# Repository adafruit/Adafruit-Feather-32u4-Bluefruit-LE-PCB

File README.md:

## Adafruit Feather 32u4 Bluefruit LE PCB

<a href="http://www.adafruit.com/products/2829"><br/>
Click here to purchase one from the Adafruit shop</a>

PCB files for the Adafruit Feather 32u4 Bluefruit LE. Format is EagleCAD schematic and board layout

For more details, check out the product page at
* https://www.adafruit.com/product/2829

### Description

Feather is the new development board from Adafruit, and like its namesake it is thin, light, and lets you fly! We designed Feather to be a new standard for portable microcontroller cores.

This is the Adafruit Feather 32u4 Bluefruit - our take on an 'all-in-one' Arduino-compatible + Bluetooth Low Energy with built in USB and battery charging. Its an Adafruit Feather 32u4 with a BTLE module, ready to rock! We have other boards in the Feather family, check'em out here.

Bluetooth Low Energy is the hottest new low-power, 2.4GHz spectrum wireless protocol. In particular, its the only wireless protocol that you can use with iOS without needing special certification and it's supported by all modern smart phones. This makes it excellent for use in portable projects that will make use of an iOS or Android phone or tablet. It also is supported in Mac OS X and Windows 8+.

[We have quite a few BTLE-capable Feathers (it's a popular protocol!) so check out our BT Feather guide for some comparison information](https://learn.adafruit.com/adafruit-feather/bluetooth-feathers).

At the Feather 32u4's heart is at ATmega32u4 clocked at 8 MHz and at 3.3V logic, a chip setup we've had tons of experience with as it's the same as the Flora. This chip has 32K of flash and 2K of RAM, with built in USB so not only does it have a USB-to-Serial program & debug capability built in with no need for an FTDI-like chip, it can also act like a mouse, keyboard, USB MIDI device, etc.

To make it easy to use for portable projects, we added a connector for any of our 3.7V Lithium polymer batteries and built in battery charging. You don't need a battery, it will run just fine straight from the micro USB connector. But, if you do have a battery, you can take it on the go, then plug in the USB to recharge. The Feather will automatically switch over to USB power when its available. We also tied the battery thru a divider to an analog pin, so you can measure and monitor the battery voltage to detect when you need a recharge.

### License

Adafruit invests time and resources providing this open source design, please support Adafruit and open-source hardware by purchasing products from [Adafruit](https://www.adafruit.com)!

Designed by Limor Fried/Ladyada for Adafruit Industries.

Creative Commons Attribution/Share-Alike, all text above must be included in any redistribution. See license.txt for additional details.

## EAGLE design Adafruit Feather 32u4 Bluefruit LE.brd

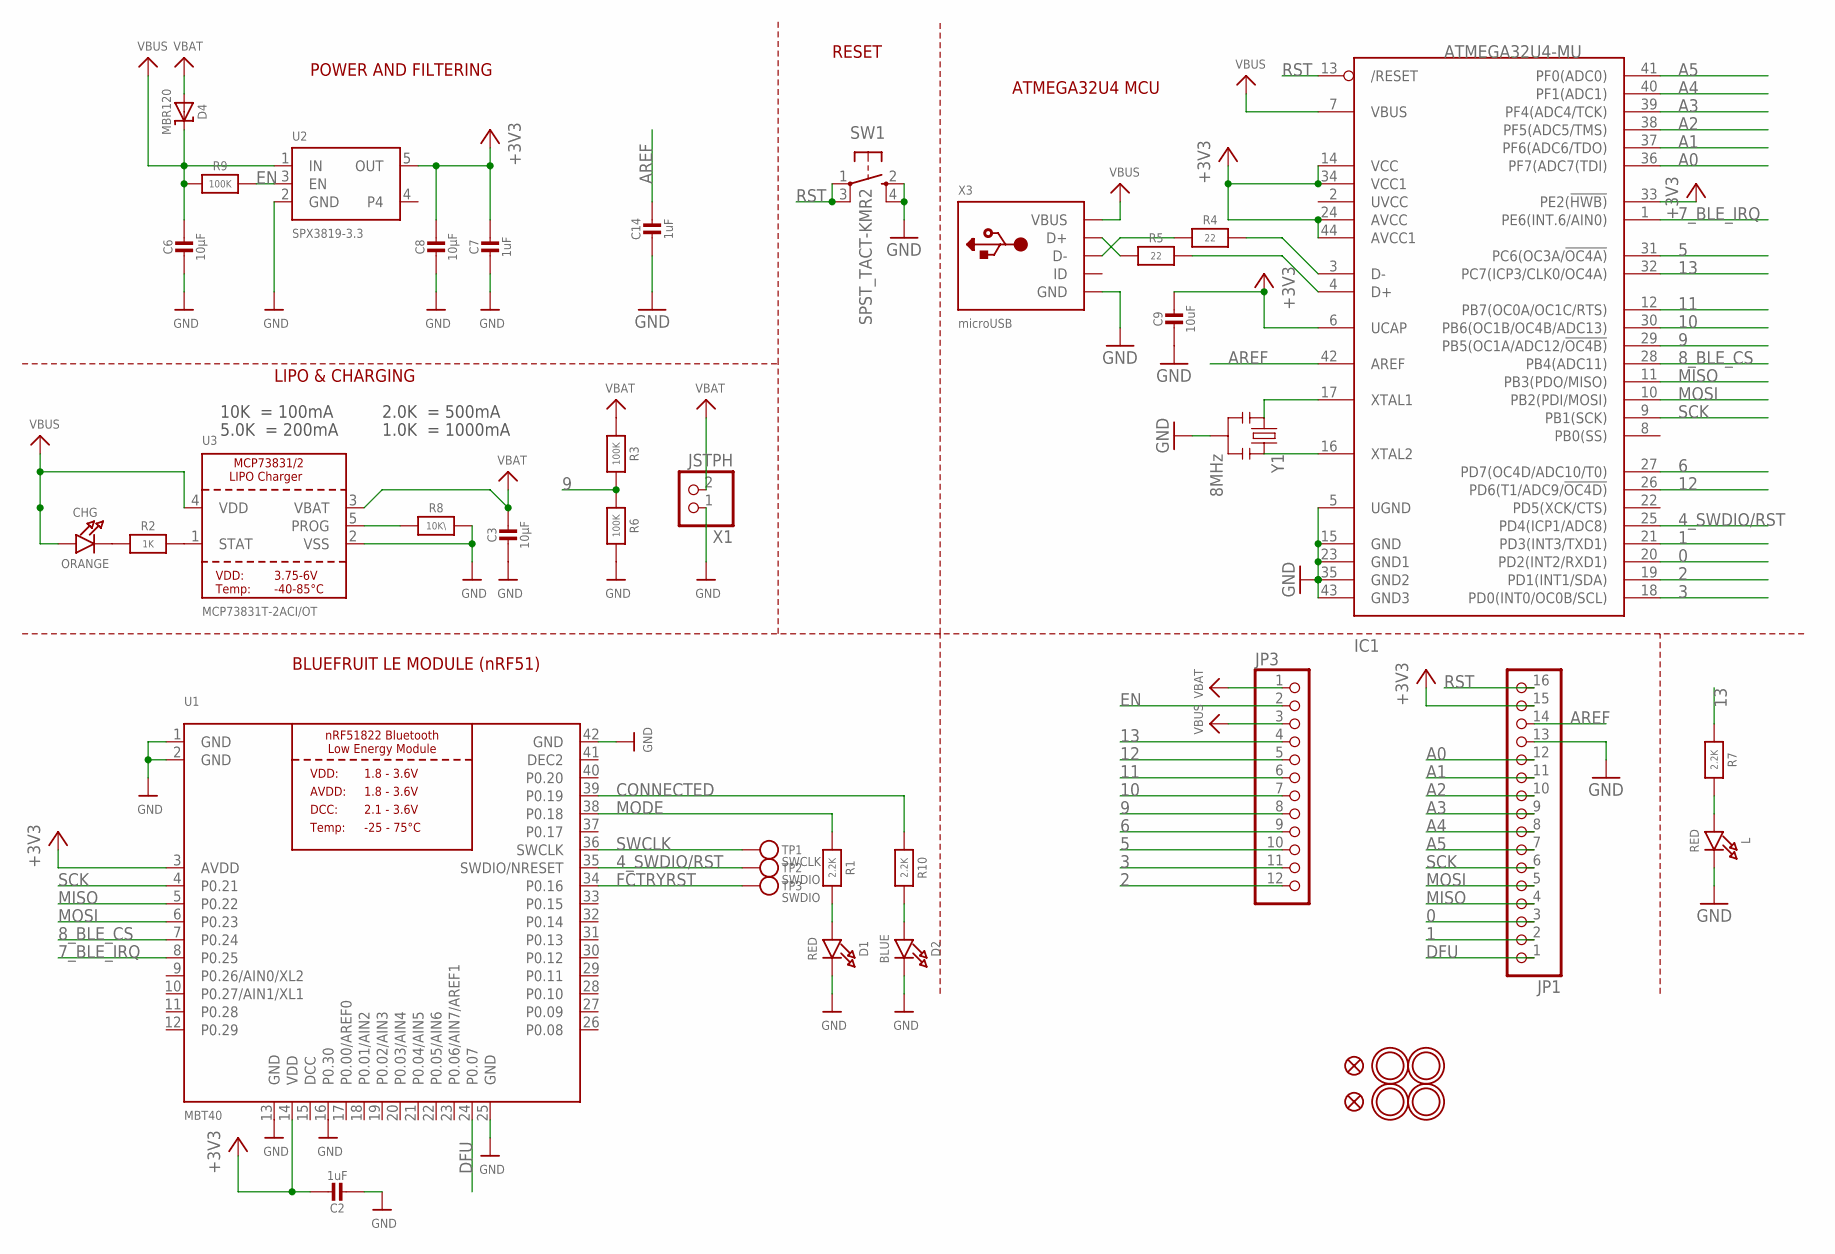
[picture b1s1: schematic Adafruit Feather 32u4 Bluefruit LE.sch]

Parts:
C2, C7, C14: 1uF; 0603-NO
C3, C6, C8: 10µF; 0805-NO
C9: 10uF; _0805MP
CHG: ORANGE; CHIPLED_0805_NOOUTLINE
D1: RED; CHIPLED_0805_NOOUTLINE
D2: BLUE; CHIPLED_0805_NOOUTLINE
D4: MBR120; SOD-123
IC1: ATMEGA32U4-MU; TQFN44_7MM
JP1: HEADER-1X16ROUND; 1X16_ROUND
JP3: HEADER-1X12; 1X12_ROUND
L: RED; CHIPLED_0805_NOOUTLINE
R1, R7, R10: 2.2K; 0603-NO
R2: 1K; 0603-NO
R3, R6, R9: 100K; 0603-NO
R4, R5: 22; 0603-NO
R8: 10K\; 0603-NO
SW1: SPST_TACT-KMR2; KMR2
TP1: SWCLK; PAD-1.5X2.0
TP2, TP3: SWDIO; PAD-1.5X2.0
U1: MBT40; BLE_MODULE_RAYTAC_MDBT40
U2: SPX3819-3.3; SOT23-5
U3: MCP73831T-2ACI/OT; SOT23-5
U$6, U$24, U$31, U$32: MOUNTINGHOLE2.5; MOUNTINGHOLE_2.5_PLATED
U$34, U$35: FIDUCIAL""; FIDUCIAL_1MM
X1: JSTPH; JSTPH2
X3: microUSB; 4UCONN_20329_V2
Y1: 8MHz; RESONATOR-SMD

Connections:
0: IC1.20 (PD2(INT2/RXD1)), JP1.3
1: IC1.21 (PD3(INT3/TXD1)), JP1.2
2: IC1.19 (PD1(INT1/SDA)), JP3.12
3: IC1.18 (PD0(INT0/OC0B/SCL)), JP3.11
4_SWDIO/RST: IC1.25 (PD4(ICP1/ADC8)), TP2.P$1, U1.35 (SWDIO/NRESET)
5: IC1.31 (PC6(OC3A/!OC4A)), JP3.10
6: IC1.27 (PD7(OC4D/ADC10/T0)), JP3.9
7_BLE_IRQ: IC1.1 (PE6(INT.6/AIN0)), U1.8 (P0.25)
8_BLE_CS: IC1.28 (PB4(ADC11)), U1.7 (P0.24)
9: IC1.29 (PB5(OC1A/ADC12/!OC4B)), JP3.8, R3.2, R6.1
10: IC1.30 (PB6(OC1B/OC4B/ADC13)), JP3.7
11: IC1.12 (PB7(OC0A/OC1C/RTS)), JP3.6
12: IC1.26 (PD6(T1/ADC9/!OC4D)), JP3.5
13: IC1.32 (PC7(ICP3/CLK0/OC4A)), JP3.4, R7.1
+3V3: C2.1, C7.1, C8.1, C9.1, IC1.6 (UCAP), IC1.14 (VCC), IC1.24 (AVCC), IC1.33 (PE2(!HWB)), IC1.34 (VCC1), IC1.44 (AVCC1), JP1.15, U1.3 (AVDD), U1.14 (VDD), U2.5 (OUT)
A0: IC1.36 (PF7(ADC7(TDI)), JP1.12
A1: IC1.37 (PF6(ADC6/TDO)), JP1.11
A2: IC1.38 (PF5(ADC5/TMS)), JP1.10
A3: IC1.39 (PF4(ADC4/TCK)), JP1.9
A4: IC1.40 (PF1(ADC1)), JP1.8
A5: IC1.41 (PF0(ADC0)), JP1.7
AREF: C14.1, IC1.42 (AREF), JP1.14
CONNECTED: R10.1, U1.39 (P0.19)
D+: IC1.4 (D+), R5.2
D-: IC1.3 (D-), R4.2
DCC: U1.15 (DCC)
DEC2: U1.41 (DEC2)
DFU: JP1.1, U1.24 (P0.07)
EN: JP3.2, R9.2, U2.3 (EN)
FCTRYRST: TP3.P$1, U1.34 (P0.16)
GND: C2.2, C3.2, C6.2, C7.2, C8.2, C9.2, C14.2, D1.C, D2.C, IC1.5 (UGND), IC1.15 (GND), IC1.23 (GND1), IC1.35 (GND2), IC1.43 (GND3), JP1.13, L.C, R6.2, R8.2, SW1.2 (S), SW1.4 (S1), U1.1 (GND), U1.2 (GND), U1.13 (GND), U1.16 (P0.30), U1.25 (GND), U1.42 (GND), U2.2 (GND), U3.2 (VSS), X1.1, X3.BASE@1 (GND), X3.BASE@2 (GND), X3.GND, X3.SPRT@1 (GND), X3.SPRT@2 (GND), X3.SPRT@3 (GND), X3.SPRT@4 (GND), Y1.2
MISO: IC1.11 (PB3(PDO/MISO)), JP1.4, U1.5 (P0.22)
MODE: R1.1, U1.38 (P0.18)
MOSI: IC1.10 (PB2(PDI/MOSI)), JP1.5, U1.6 (P0.23)
unnamed: CHG.C, R2.1
unnamed: L.A, R7.2
unnamed: R2.2, U3.1 (STAT)
unnamed: R8.1, U3.5 (PROG)
unnamed: D1.A, R1.2
unnamed: D2.A, R10.2
unnamed: IC1.16 (XTAL2), Y1.3
unnamed: IC1.17 (XTAL1), Y1.1
unnamed: R5.1, X3.D+
unnamed: R4.1, X3.D-
RST: IC1.13 (/RESET), JP1.16, SW1.1, SW1.3 (P1)
SCK: IC1.9 (PB1(SCK)), JP1.6, U1.4 (P0.21)
SWCLK: TP1.P$1, U1.36 (SWCLK)
VBAT: C3.1, D4.A, JP3.1, R3.1, U3.3 (VBAT), X1.2
VBUS: C6.1, CHG.A, D4.C, IC1.7 (VBUS), JP3.3, R9.1, U2.1 (IN), U3.4 (VDD), X3.VBUS

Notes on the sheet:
POWER AND FILTERING
BLUEFRUIT LE MODULE (nRF51)
RESET
ATMEGA32U4 MCU
10K = 100mA
5.0K = 200mA
2.0K = 500mA
1.0K = 1000mA
LIPO & CHARGING

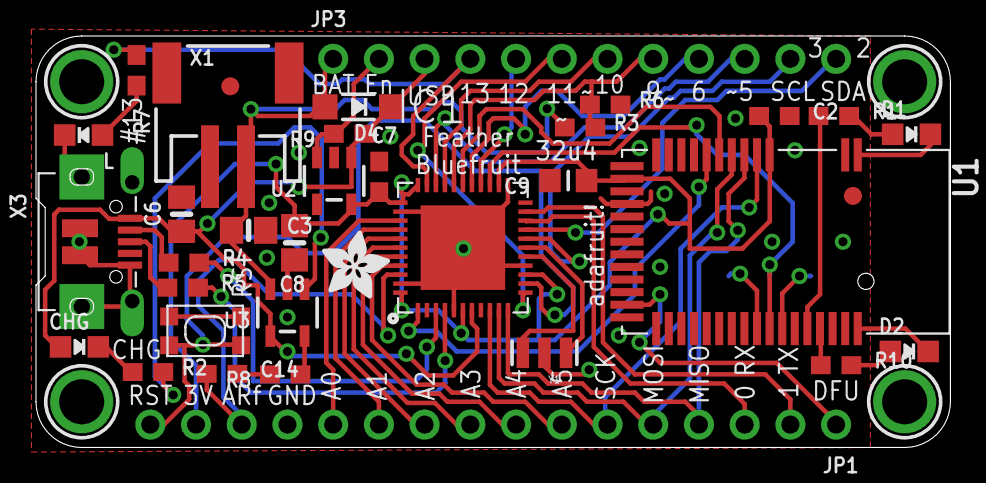
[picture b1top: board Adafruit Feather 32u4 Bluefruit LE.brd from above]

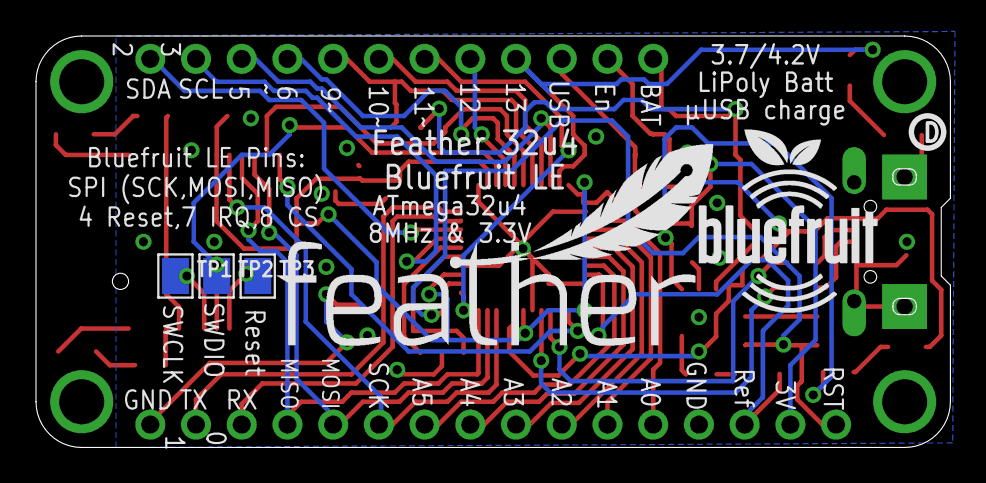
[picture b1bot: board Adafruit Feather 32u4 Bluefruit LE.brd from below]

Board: 2 copper layers, 50.8 x 22.9 mm, 45 parts (6 on the bottom side), 47 nets.

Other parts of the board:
U$7: ADAFRUIT_3.5MM
U$9: FEATHERLOGO
U$23: PCBFEAT-REV-040
U$26: BLUEFRUITLOGO_100MM

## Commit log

2016-05-27 boom!
2022-04-13 Added Prettypins
2022-04-13 Renamed PrettyPins

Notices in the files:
parts and their libraries:
microbuilder: This work is placed in the public domain, and may be freely used for commercial and non-commercial work with the following conditions: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
SparkFun: Licensing: CC v3.0 Share-Alike You are welcome to use this library for commercial purposes.
